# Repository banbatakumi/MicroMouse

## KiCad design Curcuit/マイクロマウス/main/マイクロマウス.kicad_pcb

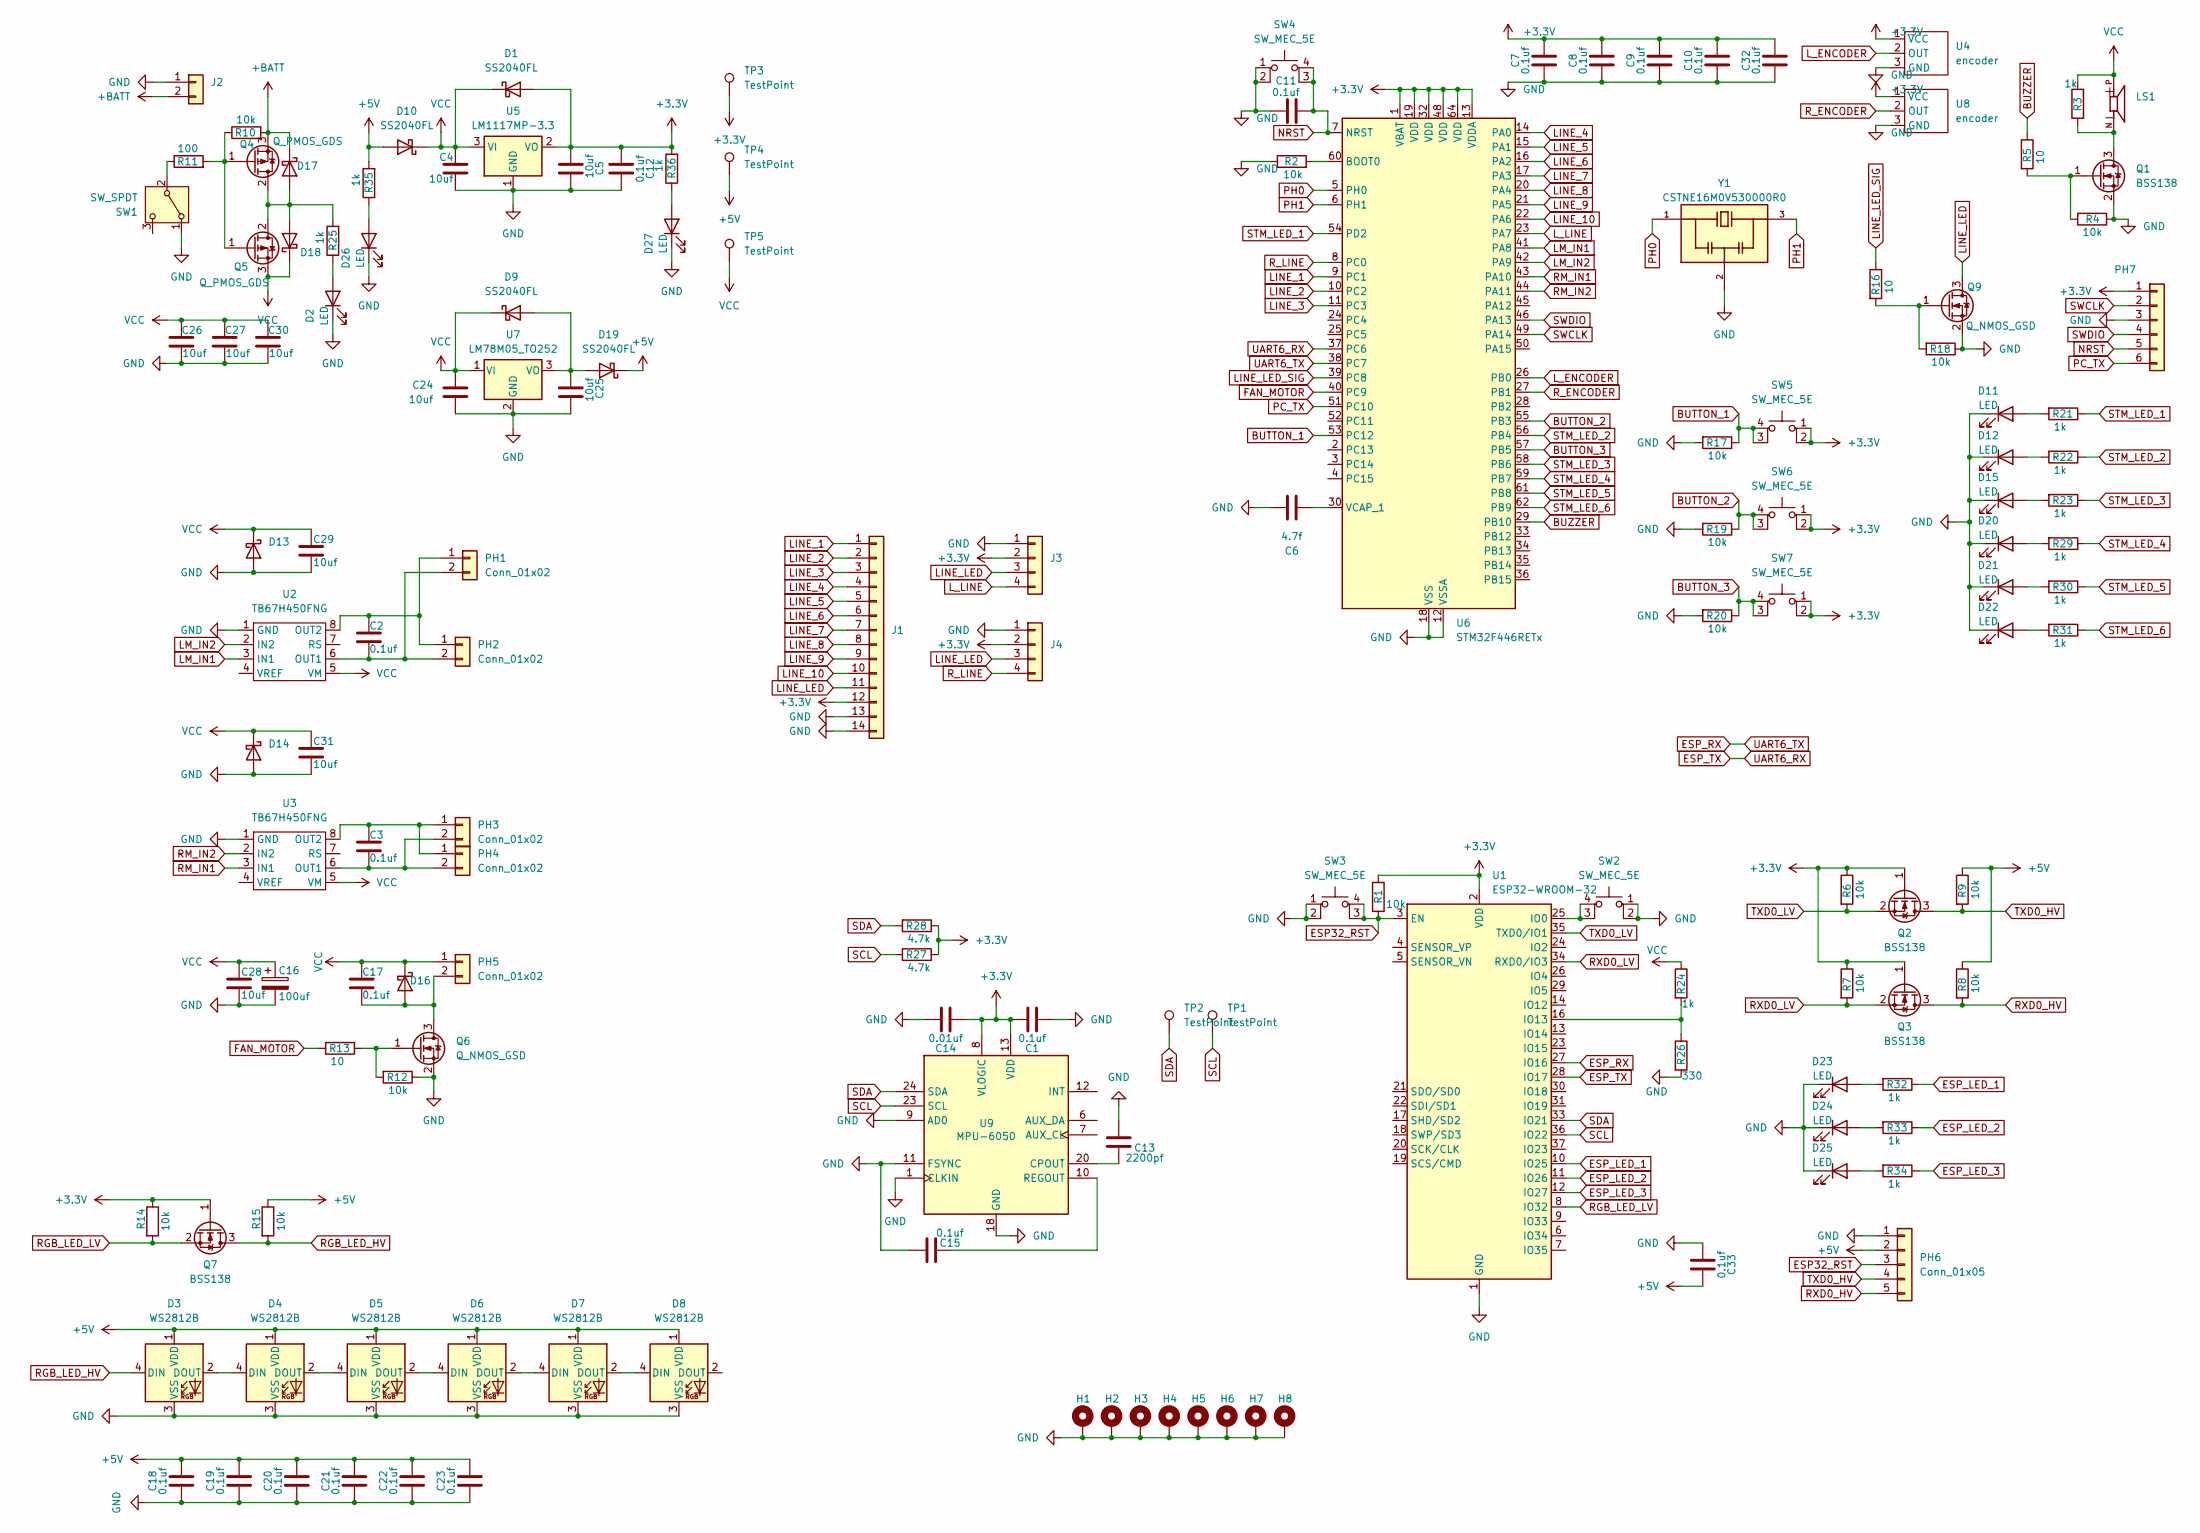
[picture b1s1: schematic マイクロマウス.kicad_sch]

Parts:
C1, C2, C3, C7, C8, C9, C10, C11, C12, C15, C17, C18, C19, C20, C21, C22, C23, C32, C33: 0.1uf; C_0603_1608Metric
C4, C5, C24, C25, C26, C27, C28, C29, C30, C31: 10uf; C_0805_2012Metric
C6: 4.7f; C_0603_1608Metric
C13: 2200pf; C_0603_1608Metric
C14: 0.01uf; C_0603_1608Metric
C16: 100uf; CP_Radial_D6.3mm_P2.50mm
D1, D9, D10, D13, D14, D16, D17, D18, D19: SS2040FL; D_SOD-123
D2, D11, D12, D15, D20, D21, D22, D23, D24, D25, D26, D27: LED; LED_0603_1608Metric
D3, D4, D5, D6, D7, D8: WS2812B; LED_WS2812B_PLCC4_5.0x5.0mm_P3.2mm
H1, H2, H3, H4, H5, H6, H7, H8: MountingHole_Pad; MountingHole_2.2mm_M2_Pad_Via
J1: Conn_01x14; Hirose_FH12-14S-0.5SH_1x14-1MP_P0.50mm_Horizontal
J2: Conn_01x02; JST_XH_B2B-XH-A_1x02_P2.50mm_Vertical
J3, J4: Conn_01x04; JST_PH_B4B-PH-K_1x04_P2.00mm_Vertical
LS1: PKLCS1212E4001-R1; SPKR_PKLCS1212E4001-R1; PARTREV January 22, 2018
PH1, PH2, PH3, PH4, PH5: Conn_01x02; JST_PH_B2B-PH-K_1x02_P2.00mm_Vertical
PH6: Conn_01x05; JST_PH_B5B-PH-K_1x05_P2.00mm_Vertical
PH7: Conn_01x06; JST_PH_B6B-PH-K_1x06_P2.00mm_Vertical
Q1, Q2, Q3, Q7: BSS138; SOT-23
Q4, Q5: Q_PMOS_GDS; TO-252-2
Q6, Q9: Q_NMOS_GSD; TSOT-23
R1, R2, R4, R6, R7, R8, R9, R10, R12, R14, R15, R17, R18, R19, R20: 10k; R_0603_1608Metric
R3, R21, R22, R23, R24, R25, R29, R30, R31, R32, R33, R34, R35, R36: 1k; R_0603_1608Metric
R5, R13, R16: 10; R_0603_1608Metric
R11: 100; R_0603_1608Metric
R26: 330; R_0603_1608Metric
R27, R28: 4.7k; R_0603_1608Metric
SW1: SW_SPDT; SS-12SDP2
SW2, SW3, SW4, SW5, SW6, SW7: SW_MEC_5E; SW4_SKRPABE010_ALPS
TP1, TP2, TP3, TP4, TP5: TestPoint; TestPoint_THTPad_D1.5mm_Drill0.7mm
U1: ESP32-WROOM-32
U2, U3: TB67H450FNG; HSOP-8-1EP_3.9x4.9mm_P1.27mm_EP2.3x2.3mm
U4, U8: encoder
U5: LM1117MP-3.3; SOT-223-3_TabPin2
U6: STM32F446RETx; LQFP-64_10x10mm_P0.5mm
U7: LM78M05_TO252; TO-252-2
U9: MPU-6050; InvenSense_QFN-24_4x4mm_P0.5mm
Y1: CSTNE16M0V530000R0; OSC_CSTNE16M0V530000R0; PARTREV JGC42-8853B

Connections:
+3.3V: C1.2, C5.1, C7.2, C8.2, C9.2, C10.2, C12.1, C14.1, C32.2, D1.2 (A), J1.12, J3.2, J4.2, PH7.1, Q2.1 (G), Q3.1 (G), Q7.1 (G), R1.1, R6.1, R7.1, R14.1, R27.1, R28.1, R36.2, SW5.1, SW5.2, SW6.1, SW6.2, SW7.1, SW7.2, TP3.1, U1.2 (VDD), U4.1 (VCC), U5.2 (VO), U6.1 (VBAT), U6.13 (VDDA), U6.19 (VDD), U6.32 (VDD), U6.48 (VDD), U6.64 (VDD), U8.1 (VCC), U9.8 (VLOGIC), U9.13 (VDD)
+5V: C18.2, C19.2, C20.2, C21.2, C22.2, C23.2, C33.2, D3.1 (VDD), D4.1 (VDD), D5.1 (VDD), D6.1 (VDD), D7.1 (VDD), D8.1 (VDD), D10.2 (A), D19.1 (K), PH6.2, R8.1, R9.1, R15.1, R35.2, TP4.1
+BATT: D17.1 (K), J2.2, Q4.3 (S), R10.2
BUTTON_1: R17.1, SW5.3 (K), SW5.4 (A), U6.53 (PC12)
BUTTON_2: R19.1, SW6.3 (K), SW6.4 (A), U6.55 (PB3)
BUTTON_3: R20.1, SW7.3 (K), SW7.4 (A), U6.57 (PB5)
BUZZER: R5.1, U6.29 (PB10)
ESP32_RST: PH6.3, R1.2, SW3.3 (K), SW3.4 (A), U1.3 (EN)
ESP_LED_1: R32.1, U1.10 (IO25)
ESP_LED_2: R33.1, U1.11 (IO26)
ESP_LED_3: R34.1, U1.12 (IO27)
ESP_RX: U1.27 (IO16), U6.38 (PC7)
ESP_TX: U1.28 (IO17), U6.37 (PC6)
FAN_MOTOR: R13.2, U6.40 (PC9)
GND: C1.1, C4.2, C5.2, C6.1, C7.1, C8.1, C9.1, C10.1, C11.1, C12.2, C13.1, C14.2, C15.2, C16.2, C18.1, C19.1, C20.1, C21.1, C22.1, C23.1, C24.2, C25.2, C26.2, C27.2, C28.1, C29.1, C30.2, C31.1, C32.1, C33.1, D2.1 (K), D3.3 (VSS), D4.3 (VSS), D5.3 (VSS), D6.3 (VSS), D7.3 (VSS), D8.3 (VSS), D11.1 (K), D12.1 (K), D13.2 (A), D14.2 (A), D15.1 (K), D20.1 (K), D21.1 (K), D22.1 (K), D23.1 (K), D24.1 (K), D25.1 (K), D26.1 (K), D27.1 (K), H1.1, H2.1, H3.1, H4.1, H5.1, H6.1, H7.1, H8.1, J1.13, J1.14, J2.1, J3.1, J4.1, PH6.1, PH7.3, Q1.2 (S), Q6.2 (S), Q9.2 (S), R2.1, R4.1, R12.1, R17.2, R18.1, R19.2, R20.2, R26.2, SW1.1 (A), SW2.1, SW2.2, SW3.1, SW3.2, SW4.1, SW4.2, U1.1 (GND), U1.15 (GND), U1.38 (GND), U1.39 (GND), U2.1 (GND), U3.1 (GND), U4.3 (GND), U5.1 (GND), U6.12 (VSSA), U6.18 (VSS), U6.31 (VSS), U6.47 (VSS), U6.63 (VSS), U7.2 (GND), U8.3 (GND), U9.1 (CLKIN), U9.9 (AD0), U9.11 (FSYNC), U9.18 (GND), Y1.2
LINE_1: J1.1, U6.9 (PC1)
LINE_2: J1.2, U6.10 (PC2)
LINE_3: J1.3, U6.11 (PC3)
LINE_4: J1.4, U6.14 (PA0)
LINE_5: J1.5, U6.15 (PA1)
LINE_6: J1.6, U6.16 (PA2)
LINE_7: J1.7, U6.17 (PA3)
LINE_8: J1.8, U6.20 (PA4)
LINE_9: J1.9, U6.21 (PA5)
LINE_10: J1.10, U6.22 (PA6)
LINE_LED: J1.11, J3.3, J4.3, Q9.3 (D)
LINE_LED_SIG: R16.1, U6.39 (PC8)
LM_IN1: U2.3 (IN1), U6.41 (PA8)
LM_IN2: U2.2 (IN2), U6.42 (PA9)
L_ENCODER: U4.2 (OUT), U6.26 (PB0)
L_LINE: J3.4, U6.23 (PA7)
NRST: C11.2, PH7.5, SW4.3 (K), SW4.4 (A), U6.7 (NRST)
unnamed: D2.2 (A), R25.1
unnamed: D3.2 (DOUT), D4.4 (DIN)
unnamed: D4.2 (DOUT), D5.4 (DIN)
unnamed: D5.2 (DOUT), D6.4 (DIN)
unnamed: D6.2 (DOUT), D7.4 (DIN)
unnamed: D7.2 (DOUT), D8.4 (DIN)
unnamed: D11.2 (A), R21.2
unnamed: D12.2 (A), R22.2
unnamed: D15.2 (A), R23.2
unnamed: C17.1, D16.2 (A), PH5.2, Q6.3 (D)
unnamed: D17.2 (A), D18.2 (A), Q4.2 (D), Q5.2 (D), R25.2
unnamed: C25.1, D9.2 (A), D19.2 (A), U7.3 (VO)
unnamed: D20.2 (A), R29.2
unnamed: D21.2 (A), R30.2
unnamed: D22.2 (A), R31.2
unnamed: D23.2 (A), R32.2
unnamed: D24.2 (A), R33.2
unnamed: D25.2 (A), R34.2
unnamed: D26.2 (A), R35.1
unnamed: D27.2 (A), R36.1
unnamed: C2.2, PH1.1, PH2.1, U2.8 (OUT2)
unnamed: C2.1, PH1.2, PH2.2, U2.6 (OUT1)
unnamed: C3.2, PH3.1, PH4.1, U3.8 (OUT2)
unnamed: C3.1, PH3.2, PH4.2, U3.6 (OUT1)
unnamed: LS1.N, Q1.3 (D), R3.1
unnamed: Q1.1 (G), R4.2, R5.2
unnamed: Q4.1 (G), Q5.1 (G), R10.1, R11.2
unnamed: Q6.1 (G), R12.2, R13.1
unnamed: Q9.1 (G), R16.2, R18.2
unnamed: R11.1, SW1.2 (B)
unnamed: SW2.3 (K), SW2.4 (A), U1.25 (IO0)
unnamed: R24.2, R26.1, U1.16 (IO13)
unnamed: R2.2, U6.60 (BOOT0)
unnamed: C6.2, U6.30 (VCAP_1)
unnamed: C13.2, U9.20 (CPOUT)
unnamed: C15.1, U9.10 (REGOUT)
PC_TX: PH7.6, U6.51 (PC10)
PH0: U6.5 (PH0), Y1.1
PH1: U6.6 (PH1), Y1.3
RGB_LED_HV: D3.4 (DIN), Q7.3 (D), R15.2
RGB_LED_LV: Q7.2 (S), R14.2, U1.8 (IO32)
RM_IN1: U3.3 (IN1), U6.43 (PA10)
RM_IN2: U3.2 (IN2), U6.44 (PA11)
RXD0_HV: PH6.5, Q3.3 (D), R8.2
RXD0_LV: Q3.2 (S), R7.2, U1.34 (RXD0/IO3)
R_ENCODER: U6.27 (PB1), U8.2 (OUT)
R_LINE: J4.4, U6.8 (PC0)
SCL: R27.2, TP1.1, U1.36 (IO22), U9.23 (SCL)
SDA: R28.2, TP2.1, U1.33 (IO21), U9.24 (SDA)
STM_LED_1: R21.1, U6.54 (PD2)
STM_LED_2: R22.1, U6.56 (PB4)
STM_LED_3: R23.1, U6.58 (PB6)
STM_LED_4: R29.1, U6.59 (PB7)
STM_LED_5: R30.1, U6.61 (PB8)
STM_LED_6: R31.1, U6.62 (PB9)
SWCLK: PH7.2, U6.49 (PA14)
SWDIO: PH7.4, U6.46 (PA13)
TXD0_HV: PH6.4, Q2.3 (D), R9.2
TXD0_LV: Q2.2 (S), R6.2, U1.35 (TXD0/IO1)
VCC: C4.1, C16.1, C17.2, C24.1, C26.1, C27.1, C28.2, C29.2, C30.1, C31.2, D1.1 (K), D9.1 (K), D10.1 (K), D13.1 (K), D14.1 (K), D16.1 (K), D18.1 (K), LS1.P, PH5.1, Q5.3 (S), R3.2, R24.1, TP5.1, U2.5 (VM), U3.5 (VM), U5.3 (VI), U7.1 (VI)

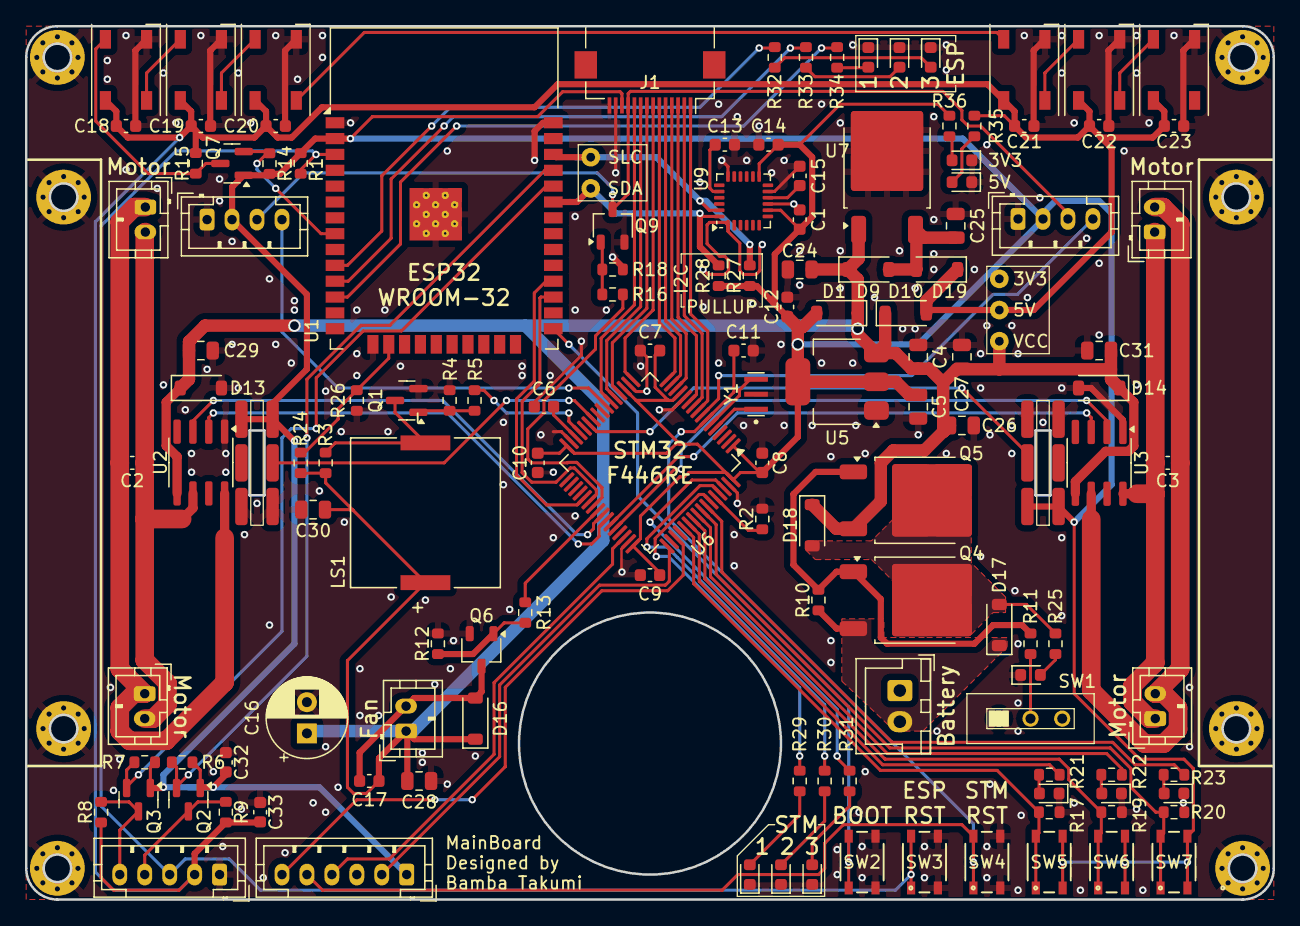
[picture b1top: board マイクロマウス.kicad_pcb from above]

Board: 2 copper layers, 100.0 x 70.0 mm, 146 parts (0 on the bottom side), 92 nets.

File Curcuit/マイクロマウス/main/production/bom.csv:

Designator,Footprint,Quantity,Value,LCSC Part #
"C1, C10, C11, C12, C15, C17, C18, C19, C2, C20, C21, C22, C23, C3, C32, C33, C7, C8, C9",0603,19,0.1uf,
C13,0603,1,2200pf,
C14,0603,1,0.01uf,
C16,CP_Radial_D6.3mm_P2.50mm,1,100uf,
"C24, C25, C26, C27, C28, C29, C30, C31, C4, C5",0805,10,10uf,
C6,0603,1,4.7f,
"D1, D10, D13, D14, D16, D17, D18, D19, D9",D_SOD-123,9,SS2040FL,
"D11, D12, D15, D2, D20, D21, D22, D23, D24, D25, D26, D27",0603,12,LED,
"D3, D4, D5, D6, D7, D8",LED_WS2812B_PLCC4_5.0x5.0mm_P3.2mm,6,WS2812B,
J1,Hirose_FH12-14S-0.5SH_1x14-1MP_P0.50mm_Horizontal,1,Conn_01x14,
J2,JST_XH_B2B-XH-A_1x02_P2.50mm_Vertical,1,Conn_01x02,
"J3, J4",JST_PH_B4B-PH-K_1x04_P2.00mm_Vertical,2,Conn_01x04,
LS1,SPKR_PKLCS1212E4001-R1,1,PKLCS1212E4001-R1,
"PH1, PH2, PH3, PH4, PH5",JST_PH_B2B-PH-K_1x02_P2.00mm_Vertical,5,Conn_01x02,
PH6,JST_PH_B5B-PH-K_1x05_P2.00mm_Vertical,1,Conn_01x05,
PH7,JST_PH_B6B-PH-K_1x06_P2.00mm_Vertical,1,Conn_01x06,
"Q1, Q2, Q3, Q7",SOT-23,4,BSS138,
"Q4, Q5",TO-252-2,2,Q_PMOS_GDS,
"Q6, Q9",TSOT-23,2,Q_NMOS_GSD,
"R1, R10, R12, R14, R15, R17, R18, R19, R2, R20, R4, R6, R7, R8, R9",0603,15,10k,
R11,0603,1,100,
"R13, R16, R5",0603,3,10,
"R21, R22, R23, R24, R25, R29, R3, R30, R31, R32, R33, R34, R35, R36",0603,14,1k,
R26,0603,1,330,
"R27, R28",0603,2,4.7k,
SW1,SS-12SDP2,1,SW_SPDT,
"SW2, SW3, SW4, SW5, SW6, SW7",SW4_SKRPABE010_ALPS,6,SW_MEC_5E,
"TP1, TP2, TP3, TP4, TP5",TestPoint_THTPad_D1.5mm_Drill0.7mm,5,TestPoint,
U1,ESP32-WROOM-32,1,ESP32-WROOM-32,
"U2, U3",HSOP-8-1EP_3.9x4.9mm_P1.27mm_EP2.3x2.3mm,2,TB67H450FNG,
"U4, U8",encoder,2,encoder,
U5,SOT-223-3_TabPin2,1,LM1117MP-3.3,
U6,LQFP-64_10x10mm_P0.5mm,1,STM32F446RETx,
U7,TO-252-2,1,LM78M05_TO252,
U9,InvenSense_QFN-24_4x4mm_P0.5mm,1,MPU-6050,
Y1,OSC_CSTNE16M0V530000R0,1,CSTNE16M0V530000R0,

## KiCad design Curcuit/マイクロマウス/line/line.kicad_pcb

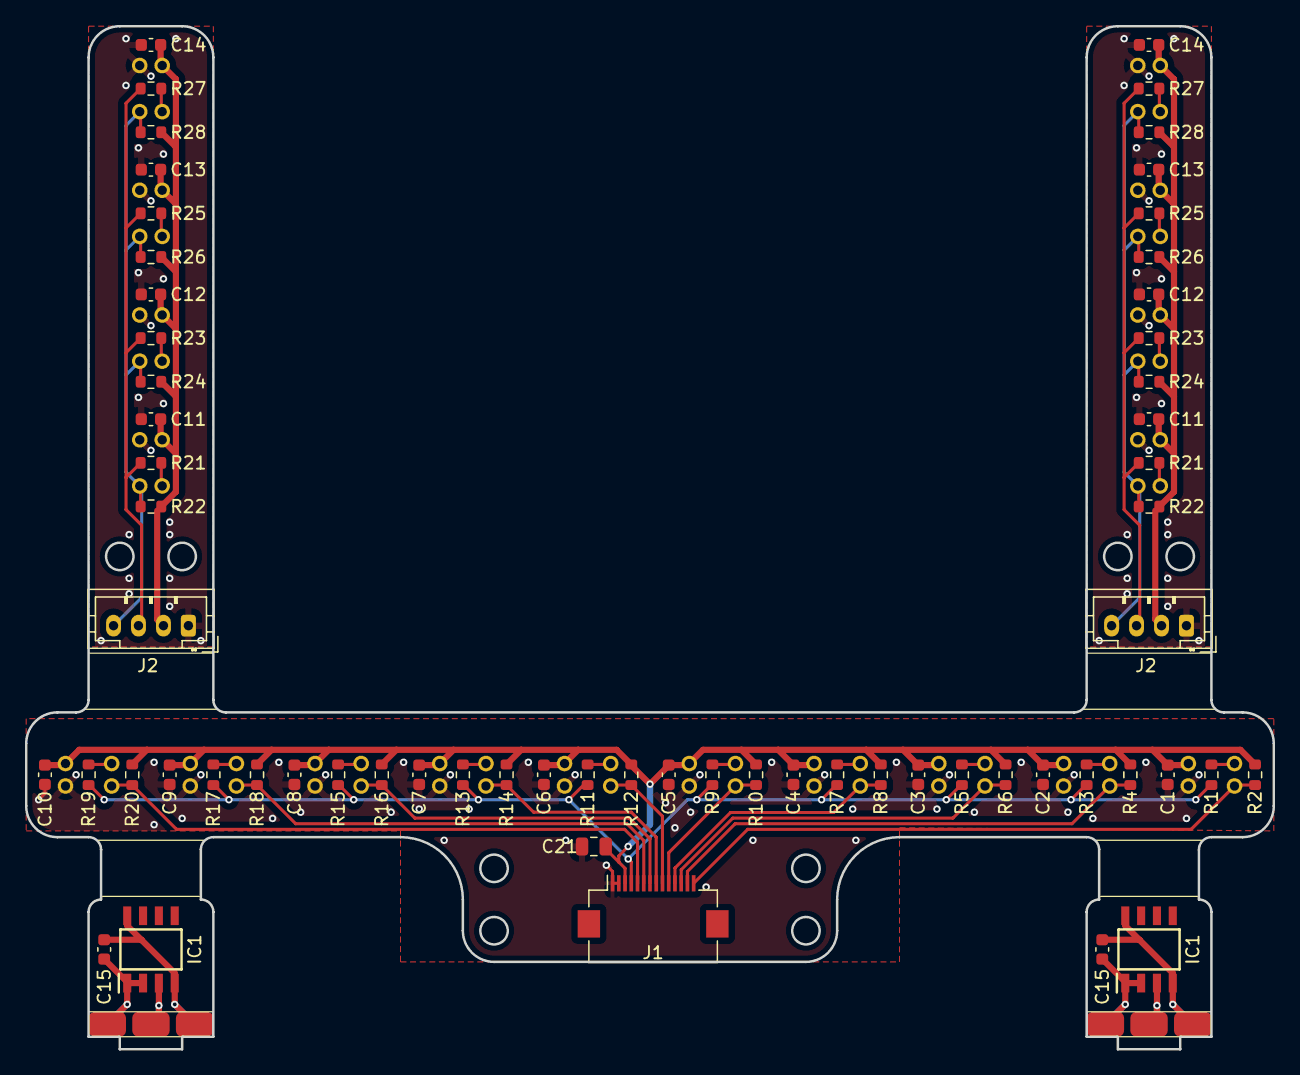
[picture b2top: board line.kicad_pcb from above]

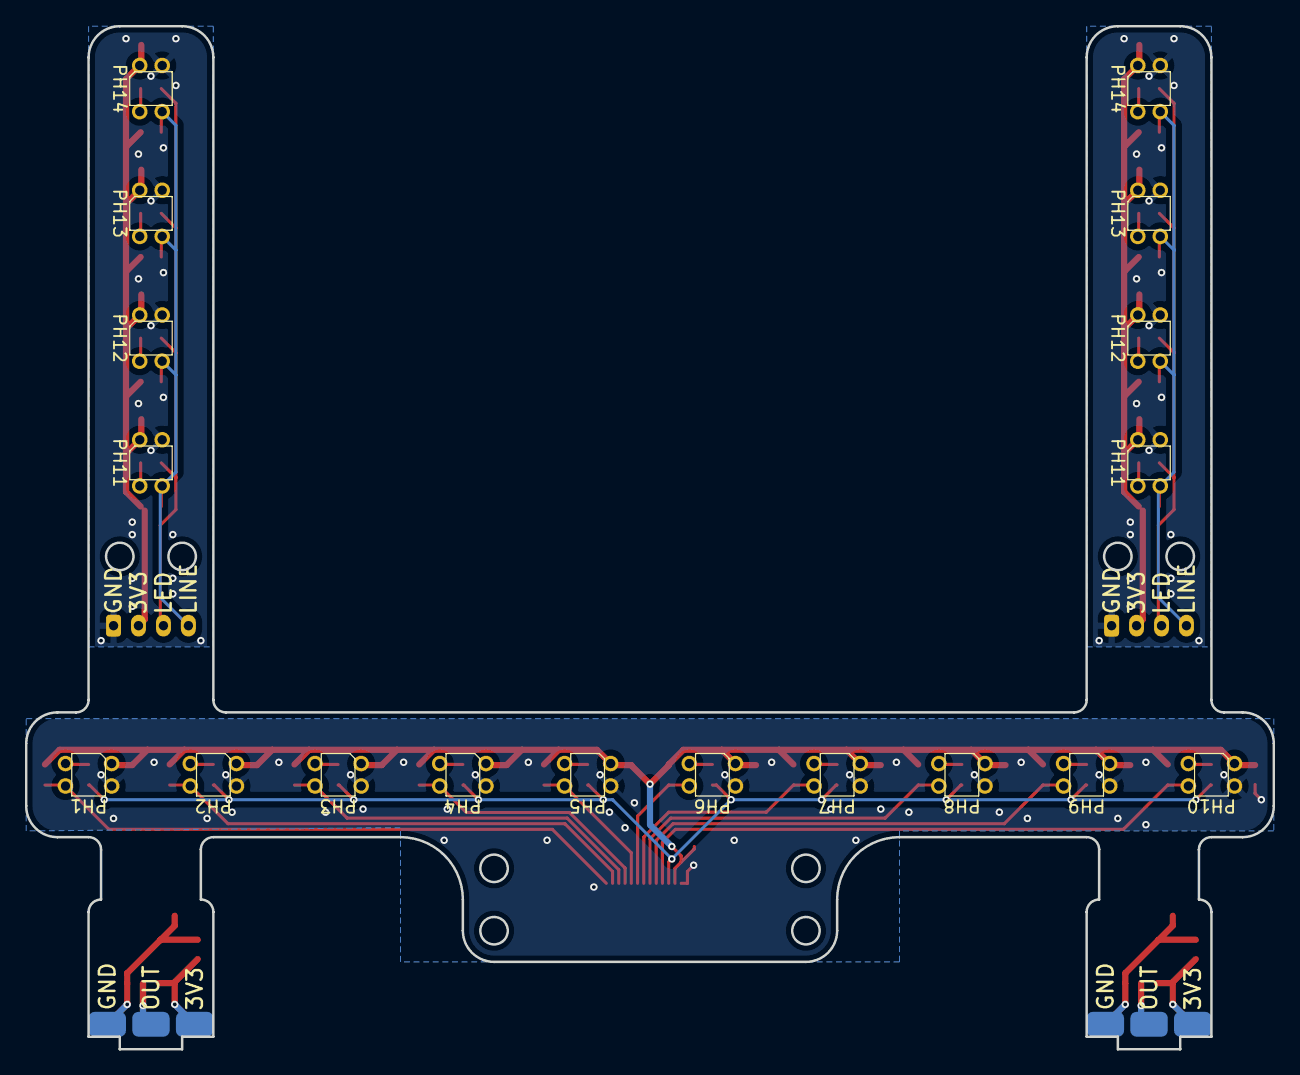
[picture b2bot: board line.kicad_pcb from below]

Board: 2 copper layers, 100.0 x 82.0 mm, 82 parts (18 on the bottom side), 29 nets.

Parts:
C1, C2, C3, C4, C5, C6, C7, C8, C9, C10, C11, C11#2, C12, C12#2, C13, C13#2, C14, C14#2, C15, C15#2: 0.1f; C_0603_1608Metric
C21: 0.1f; C_0805_2012Metric
IC1, IC1#2: AS5600-ASOT; SOIC127P600X175-8N
J1: Conn_01x14; Hirose_FH12-14S-0.5SH_1x14-1MP_P0.50mm_Horizontal
J2, J2#2: Conn_01x04; JST_PH_B4B-PH-K_1x04_P2.00mm_Vertical
PH1, PH2, PH3, PH4, PH5, PH6, PH7, PH8, PH9, PH10, PH11, PH11#2, PH12, PH12#2, PH13, PH13#2, PH14, PH14#2: LBR-123F
R1, R3, R5, R7, R9, R11, R13, R15, R17, R19, R21, R21#2, R23, R23#2, R25, R25#2, R27, R27#2: 100; R_0603_1608Metric
R2, R4, R6, R8, R10, R12, R14, R16, R18, R20, R22, R22#2, R24, R24#2, R26, R26#2, R28, R28#2: 10k; R_0603_1608Metric
U1, U1#2: encoder

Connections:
+3V3: C1.1, C2.1, C3.1, C4.1, C5.1, C6.1, C7.1, C8.1, C9.1, C10.1, C11.1, C11#2.1, C12.1, C12#2.1, C13.1, C13#2.1, C14.1, C14#2.1, C15.1, C15#2.1, C21.1, IC1.1 (VDD5V), IC1.2 (VDD3V3), IC1#2.1 (VDD5V), IC1#2.2 (VDD3V3), J1.3, J2.2, J2#2.2, PH1.1 (A), PH2.1 (A), PH3.1 (A), PH4.1 (A), PH5.1 (A), PH6.1 (A), PH7.1 (A), PH8.1 (A), PH9.1 (A), PH10.1 (A), PH11.1 (A), PH11#2.1 (A), PH12.1 (A), PH12#2.1 (A), PH13.1 (A), PH13#2.1 (A), PH14.1 (A), PH14#2.1 (A), R2.1, R4.1, R6.1, R8.1, R10.1, R12.1, R14.1, R16.1, R18.1, R20.1, R22.1, R22#2.1, R24.1, R24#2.1, R26.1, R26#2.1, R28.1, R28#2.1, U1.3 (GND), U1#2.3 (GND)
GND: C1.2, C2.2, C3.2, C4.2, C5.2, C6.2, C7.2, C8.2, C9.2, C10.2, C11.2, C11#2.2, C12.2, C12#2.2, C13.2, C13#2.2, C14.2, C14#2.2, C15.2, C15#2.2, C21.2, IC1.4 (GND), IC1.8 (DIR), IC1#2.4 (GND), IC1#2.8 (DIR), J1.1, J1.2, J2.1, J2#2.1, PH1.3 (E), PH2.3 (E), PH3.3 (E), PH4.3 (E), PH5.3 (E), PH6.3 (E), PH7.3 (E), PH8.3 (E), PH9.3 (E), PH10.3 (E), PH11.3 (E), PH11#2.3 (E), PH12.3 (E), PH12#2.3 (E), PH13.3 (E), PH13#2.3 (E), PH14.3 (E), PH14#2.3 (E), U1.1 (VCC), U1#2.1 (VCC)
LED: J1.4, J2.3, J2#2.3, R1.1, R3.1, R5.1, R7.1, R9.1, R11.1, R13.1, R15.1, R17.1, R19.1, R21.1, R21#2.1, R23.1, R23#2.1, R25.1, R25#2.1, R27.1, R27#2.1
LINE: J2.4, J2#2.4, PH11.4 (C), PH11#2.4 (C), PH12.4 (C), PH12#2.4 (C), PH13.4 (C), PH13#2.4 (C), PH14.4 (C), PH14#2.4 (C), R22.2, R22#2.2, R24.2, R24#2.2, R26.2, R26#2.2, R28.2, R28#2.2
LINE_1: J1.14, PH1.4 (C), R2.2
LINE_2: J1.13, PH2.4 (C), R4.2
LINE_3: J1.12, PH3.4 (C), R6.2
LINE_4: J1.11, PH4.4 (C), R8.2
LINE_5: J1.10, PH5.4 (C), R10.2
LINE_6: J1.9, PH6.4 (C), R12.2
LINE_7: J1.8, PH7.4 (C), R14.2
LINE_8: J1.7, PH8.4 (C), R16.2
LINE_9: J1.6, PH9.4 (C), R18.2
LINE_10: J1.5, PH10.4 (C), R20.2
unnamed: IC1.3 (OUT), IC1#2.3 (OUT), U1.2 (OUT), U1#2.2 (OUT)
unnamed: PH1.2 (K), R1.2
unnamed: PH2.2 (K), R3.2
unnamed: PH3.2 (K), R5.2
unnamed: PH4.2 (K), R7.2
unnamed: PH5.2 (K), R9.2
unnamed: PH6.2 (K), R11.2
unnamed: PH7.2 (K), R13.2
unnamed: PH8.2 (K), R15.2
unnamed: PH9.2 (K), R17.2
unnamed: PH10.2 (K), R19.2
unnamed: PH11.2 (K), PH11#2.2 (K), R21.2, R21#2.2
unnamed: PH12.2 (K), PH12#2.2 (K), R23.2, R23#2.2
unnamed: PH13.2 (K), PH13#2.2 (K), R25.2, R25#2.2
unnamed: PH14.2 (K), PH14#2.2 (K), R27.2, R27#2.2

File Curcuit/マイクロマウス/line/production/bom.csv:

Designator,Footprint,Quantity,Value,LCSC Part #
"C1, C10, C11_2, C11, C12_2, C12, C13_2, C13, C14_2, C14, C15_2, C15, C2, C3, C4, C5, C6, C7, C8, C9",0603,20,0.1f,
C21,0805,1,0.1f,
"IC1_2, IC1",SOIC127P600X175-8N,2,AS5600-ASOT,
J1,Hirose_FH12-14S-0.5SH_1x14-1MP_P0.50mm_Horizontal,1,Conn_01x14,
"J2_2, J2",JST_PH_B4B-PH-K_1x04_P2.00mm_Vertical,2,Conn_01x04,
"PH1, PH10, PH11_2, PH11, PH12_2, PH12, PH13_2, PH13, PH14_2, PH14, PH2, PH3, PH4, PH5, PH6, PH7, PH8, PH9",LBR-123F,18,LBR-123F,
"R1, R11, R13, R15, R17, R19, R21_2, R21, R23_2, R23, R25_2, R25, R27_2, R27, R3, R5, R7, R9",0603,18,100,
"R10, R12, R14, R16, R18, R2, R20, R22_2, R22, R24_2, R24, R26_2, R26, R28_2, R28, R4, R6, R8",0603,18,10k,
"U1_2, U1",encoder,2,encoder,

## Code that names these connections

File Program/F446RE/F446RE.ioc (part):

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Mcu.Name=STM32F446R(C-E)Tx
Mcu.Package=LQFP64
Mcu.UserName=STM32F446RETx
PA0-WKUP.GPIOParameters=GPIO_PuPd,GPIO_Label,GPIO_Mode
PA0-WKUP.GPIO_Label=LINE4
PA0-WKUP.GPIO_Mode=GPIO_MODE_ANALOG
PA0-WKUP.GPIO_PuPd=GPIO_NOPULL
PA0-WKUP.Signal=ADCx_IN0
PA1.GPIOParameters=GPIO_PuPd,GPIO_Label,GPIO_Mode
PA1.GPIO_Label=LINE5
PA1.GPIO_Mode=GPIO_MODE_ANALOG
PA1.GPIO_PuPd=GPIO_NOPULL
PA1.Signal=ADCx_IN1
PA10.GPIOParameters=GPIO_Label
PA10.GPIO_Label=RA_MOTOR
PA10.Signal=S_TIM1_CH3
PA11.GPIOParameters=GPIO_Label
PA11.GPIO_Label=RB_MOTOR
PA11.Signal=S_TIM1_CH4
PA13.Signal=SYS_JTMS-SWDIO
PA14.Signal=SYS_JTCK-SWCLK
PA2.GPIOParameters=GPIO_PuPd,GPIO_Label,GPIO_Mode
PA2.GPIO_Label=LINR6
PA2.GPIO_Mode=GPIO_MODE_ANALOG
PA2.GPIO_PuPd=GPIO_NOPULL
PA2.Signal=ADCx_IN2
PA3.GPIOParameters=GPIO_PuPd,GPIO_Label,GPIO_Mode
PA3.GPIO_Label=LINE7
PA3.GPIO_Mode=GPIO_MODE_ANALOG
PA3.GPIO_PuPd=GPIO_NOPULL
PA3.Signal=ADCx_IN3
PA4.GPIOParameters=GPIO_PuPd,GPIO_Label,GPIO_Mode
PA4.GPIO_Label=LINE8
PA4.GPIO_Mode=GPIO_MODE_ANALOG
PA4.GPIO_PuPd=GPIO_NOPULL
PA4.Signal=ADCx_IN4
PA5.GPIOParameters=GPIO_PuPd,GPIO_Label,GPIO_Mode
PA5.GPIO_Label=LINE9
PA5.GPIO_Mode=GPIO_MODE_ANALOG
PA5.GPIO_PuPd=GPIO_NOPULL
PA5.Signal=ADCx_IN5
PA6.GPIOParameters=GPIO_PuPd,GPIO_Label,GPIO_Mode
PA6.GPIO_Label=LINE10
PA6.GPIO_Mode=GPIO_MODE_ANALOG
PA6.GPIO_PuPd=GPIO_NOPULL
PA6.Signal=ADCx_IN6
PA7.GPIOParameters=GPIO_PuPd,GPIO_Label,GPIO_Mode
PA7.GPIO_Label=LINE_L
PA7.GPIO_Mode=GPIO_MODE_ANALOG
PA7.GPIO_PuPd=GPIO_NOPULL
PA7.Signal=ADCx_IN7
PA8.GPIOParameters=GPIO_Label
PA8.GPIO_Label=LA_MOTOR
PA8.Signal=S_TIM1_CH1
PA9.GPIOParameters=GPIO_Label
PA9.GPIO_Label=LB_MOTOR
PA9.Signal=S_TIM1_CH2
PB0.Signal=ADCx_IN8
PB1.Signal=ADCx_IN9
PB10.GPIOParameters=GPIO_Label
PB10.GPIO_Label=BUZZER
PB10.Signal=S_TIM2_CH3
PB3.GPIOParameters=GPIO_Label
PB3.GPIO_Label=BUTTON2
PB3.Signal=GPIO_Input
PB4.GPIOParameters=GPIO_Label
PB4.GPIO_Label=LED2
PB4.Signal=GPIO_Output
PB5.GPIOParameters=GPIO_Label
PB5.GPIO_Label=BUTTON3
PB5.Signal=GPIO_Input
PB6.GPIOParameters=GPIO_Label
PB6.GPIO_Label=LED3
PB6.Signal=GPIO_Output
PB7.GPIOParameters=GPIO_Label
PB7.GPIO_Label=LED4
PB7.Signal=GPIO_Output
PB8.GPIOParameters=GPIO_Label
PB8.GPIO_Label=LED5
PB8.Signal=GPIO_Output
PB9.GPIOParameters=GPIO_Label
PB9.GPIO_Label=LEDH
PB9.Signal=S_TIM2_CH2
PC0.GPIOParameters=GPIO_PuPd,GPIO_Label,GPIO_Mode
PC0.GPIO_Label=LINE_R
PC0.GPIO_Mode=GPIO_MODE_ANALOG
PC0.GPIO_PuPd=GPIO_NOPULL
PC0.Signal=ADCx_IN10
PC1.GPIOParameters=GPIO_PuPd,GPIO_Label,GPIO_Mode
PC1.GPIO_Label=LINE1
PC1.GPIO_Mode=GPIO_MODE_ANALOG
PC1.GPIO_PuPd=GPIO_NOPULL
PC1.Signal=ADCx_IN11
PC10.Mode=Half_duplex(single_wire_mode)
PC10.Signal=UART4_TX
PC12.GPIOParameters=GPIO_Label
PC12.GPIO_Label=BUTTON1
PC12.Signal=GPIO_Input
PC2.GPIOParameters=GPIO_PuPd,GPIO_Label,GPIO_Mode
PC2.GPIO_Label=LINE2
PC2.GPIO_Mode=GPIO_MODE_ANALOG
PC2.GPIO_PuPd=GPIO_NOPULL
PC2.Signal=ADCx_IN12
PC3.GPIOParameters=GPIO_PuPd,GPIO_Label,GPIO_Mode
PC3.GPIO_Label=LINE3
PC3.GPIO_Mode=GPIO_MODE_ANALOG
PC3.GPIO_PuPd=GPIO_NOPULL
PC3.Signal=ADCx_IN13
PC6.Mode=Asynchronous
PC6.Signal=USART6_TX
PC7.Mode=Asynchronous
PC7.Signal=USART6_RX
PC8.GPIOParameters=GPIO_Label
PC8.GPIO_Label=LINE_LED
PC8.Signal=S_TIM3_CH3
PC9.GPIOParameters=GPIO_Label
PC9.GPIO_Label=FAN_MOTOR
PC9.Signal=S_TIM3_CH4
PD2.GPIOParameters=GPIO_Label
PD2.GPIO_Label=LED1
PD2.Signal=GPIO_Output
PH0-OSC_IN.Mode=HSE-External-Oscillator
PH0-OSC_IN.Signal=RCC_OSC_IN
PH1-OSC_OUT.Mode=HSE-External-Oscillator
PH1-OSC_OUT.Signal=RCC_OSC_OUT
RCC.HSE_VALUE=16000000
RCC.SYSCLKFreq_VALUE=80000000
RCC.SYSCLKSource=RCC_SYSCLKSOURCE_PLLCLK
board=custom

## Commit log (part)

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2024-11-03 edit README
2024-11-03 add files
2024-11-03 genarate code
2024-11-03 Lチカできた
2024-11-03 ブザー鳴らせた
2024-11-03 uart4からprintfできるようになった
2024-11-04 Makefileでビルドできた&appの追加
2024-11-04 make runで書き込み
2024-11-04 ライブラリ追加
2024-11-05 ADCをDMAで読めた
2024-11-06 ラインの位置を読めた
2024-11-07 ちょっとだけライントレースできるようになった
2024-11-07 エンコーダー読めた
2024-11-09 rad/s読めた
2024-11-09 速度制御できた
2024-11-11 コメントアウトの追加
2024-11-14 ラインの位置をmmで読めた
2024-11-16 綺麗にライントレースできた
2024-11-16 MPU6050読めた
2024-11-26 白線と黒線を切り替えできるようになった
2024-12-03 センサ値に移動平均をかけた
2024-12-05 ゲイン調整
2024-12-05 pcとTCPで通信できた
2024-12-05 RTOS実装
2024-12-06 uartで送信
2024-12-06 ESPとUART
2024-12-06 モード整理
2024-12-10 ライントレースのファイル分割
2024-12-13 GPTに生成させたコードを追加
